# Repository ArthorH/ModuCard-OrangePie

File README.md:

# ModuCard System Orange PI 5 pro adapter

## Project Status: **Ongoing**  
### REV C
**Design** ⏳ — **Fabrication** ⏳ — **Assembly** ⏳ — **Bringup** ⏳ — **Testing** ⏳
### REV B
**Design** ✅ — **Fabrication** ✅ — **Assembly** ✅ — **Bringup** ✅ — **Testing** ⛔ 
Failed: https://github.com/ArthorH/ModuCard-OrangePie/issues/6
### REV A
**Design** ✅ — **Fabrication** ✅ — **Assembly** ✅ — **Bringup** ✅ — **Testing done** ✅ 
## Key technologies:
&nbsp;&nbsp;&nbsp;&nbsp; &nbsp;&nbsp;&nbsp;&nbsp; &nbsp;&nbsp;&nbsp;&nbsp;
# Features

- 5V 8A psu for Orange PI
- Embedded USB audo interface
- Embedded USB CAN adapter
- External Fan controller
- UART debug interface
  
# Block Diagram
&nbsp;&nbsp;&nbsp;&nbsp;

# Manufactured board

# Moducard OrangePie in Zwentendorf Austria!

### Check out other projects

Orange Pie ->  https://github.com/ArthorH/ModuCard-OrangePie

ModuCard Base module -> https://github.com/ArthorH/ModuCard-base-module

ModuCard Backplane -> https://github.com/ArthorH/ModuCard-backplane

# Author
Artem Horiunov
# License 
To be added

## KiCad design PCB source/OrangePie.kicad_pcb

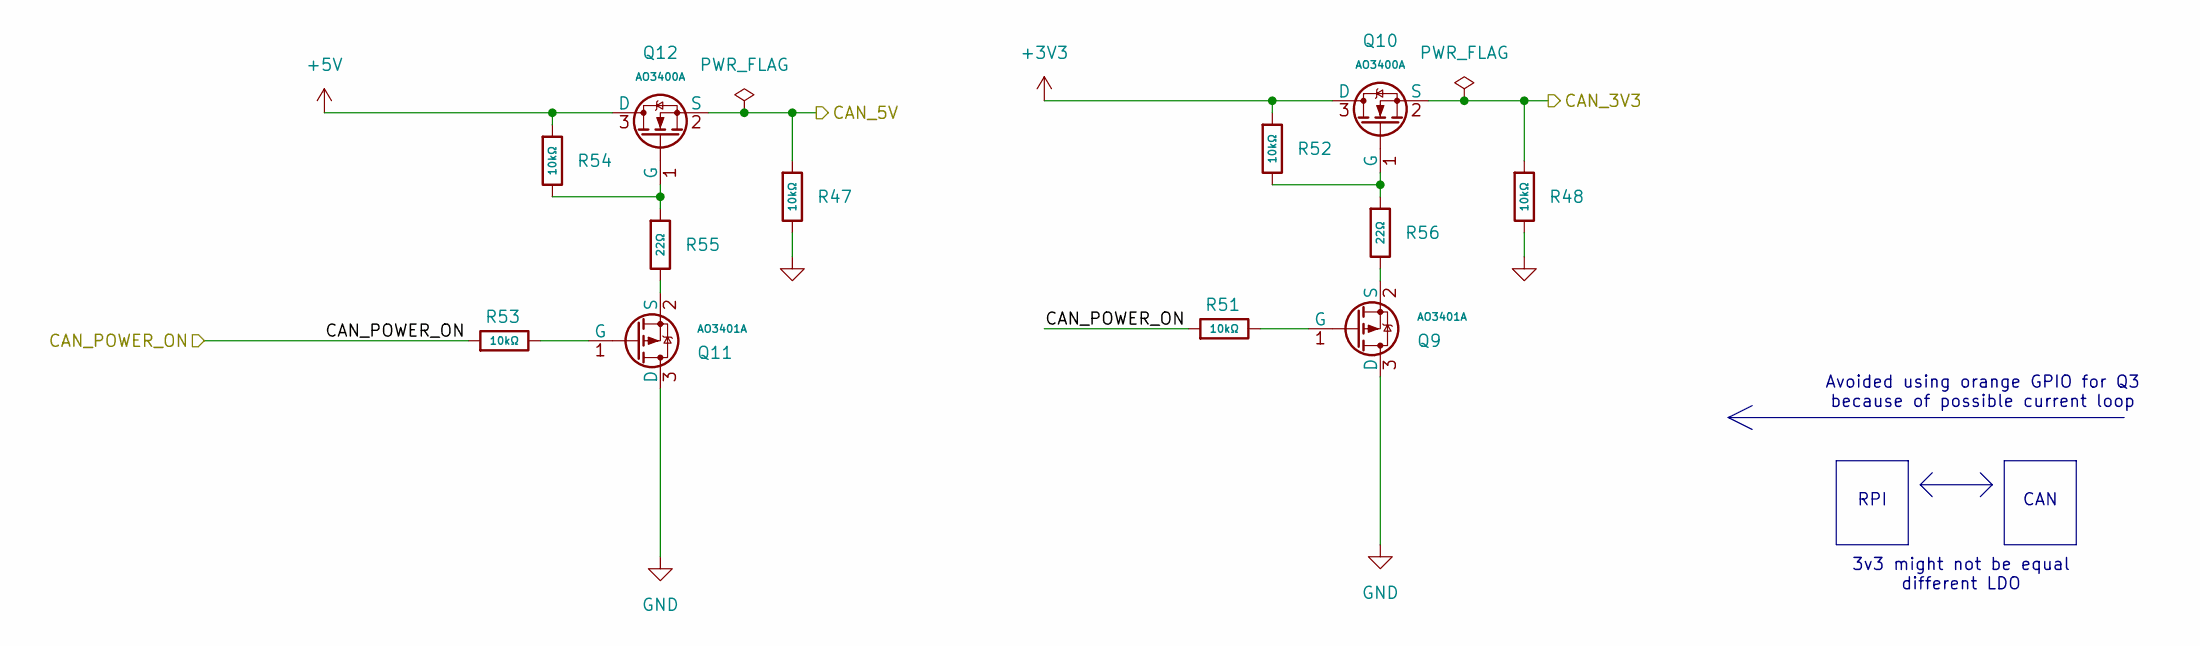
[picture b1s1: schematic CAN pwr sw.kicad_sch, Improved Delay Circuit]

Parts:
Q9, Q11: AO3401A; Q_SOT-23; Part AO3401A; LCSC C15127
Q10, Q12: AO3400A; Q_SOT-23; Part AO3400A; LCSC C20917
R47, R48, R51, R52, R53, R54: 10kΩ; R_0402; Overload Voltage (Max) 50V; Tolerance ±1%; Part 0402WGF1002TCE; LCSC C25744
R55, R56: 22Ω; R_0402; Overload Voltage (Max) 50V; Tolerance ±1%; Part 0402WGF220JTCE; LCSC C25092

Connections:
+3V3: Q10.3 (D), R52.1; also elsewhere on the board
+5V: Q12.3 (D), R54.1; also elsewhere on the board
/CAN pwr sw/CAN_3V3: Q10.2 (S), R48.1; also elsewhere on the board
/CAN pwr sw/CAN_5V: Q12.2 (S), R47.1; also elsewhere on the board
/CAN pwr sw/CAN_POWER_ON: R51.1, R53.1; also elsewhere on the board
GND: Q9.3 (D), Q11.3 (D), R47.2, R48.2; also elsewhere on the board
unnamed: Q9.1 (G), R51.2
unnamed: Q9.2 (S), R56.2
unnamed: Q10.1 (G), R52.2, R56.1
unnamed: Q11.1 (G), R53.2
unnamed: Q11.2 (S), R55.2
unnamed: Q12.1 (G), R54.2, R55.1

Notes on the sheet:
Avoided using orange GPIO for Q3 because of possible current loop
CAN
RPI
3v3 might not be equal different LDO

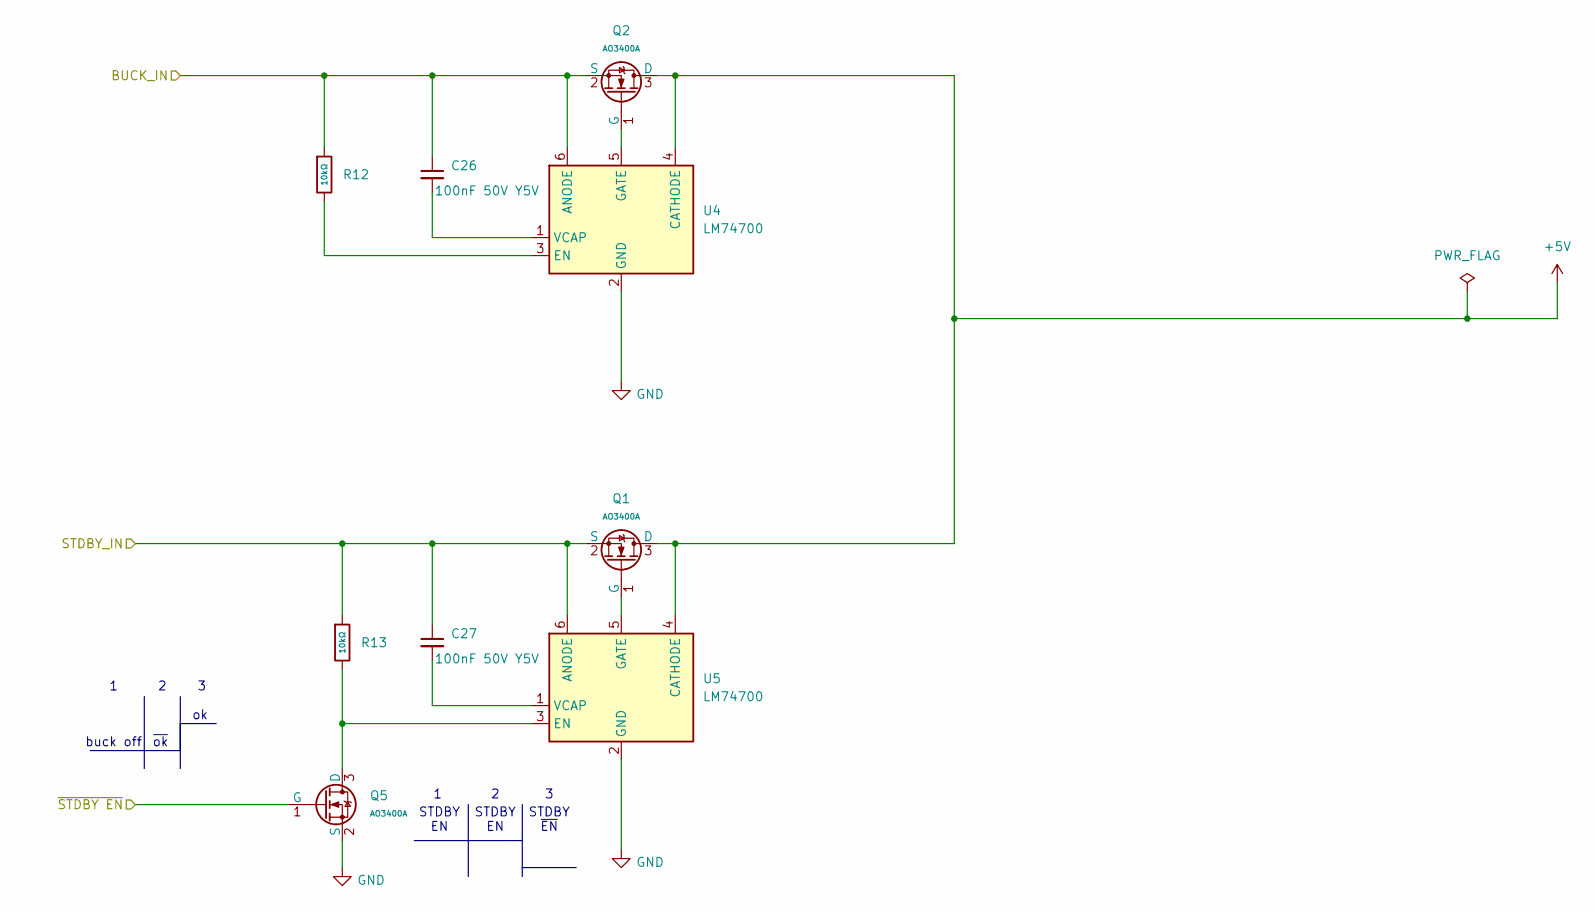
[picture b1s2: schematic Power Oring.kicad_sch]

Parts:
C26, C27: 100nF 50V Y5V; C_0402_1005Metric
Q1, Q2, Q5: AO3400A; Q_SOT-23; Part AO3400A; LCSC C20917
R12, R13: 10kΩ; R_0402; Overload Voltage (Max) 50V; Tolerance ±1%; Part 0402WGF1002TCE; LCSC C25744
U4, U5: LM74700; SOT-23-6

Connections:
+5V: Q1.3 (D), Q2.3 (D), U4.4 (CATHODE), U5.4 (CATHODE); also elsewhere on the board
/5v buck/BUCK_OUT: C26.1, Q2.2 (S), R12.1, U4.6 (ANODE); also elsewhere on the board
/5v buck/Pgood: Q5.1 (G); also elsewhere on the board
/DIN41612 connector/5v_STDBY: C27.1, Q1.2 (S), R13.1, U5.6 (ANODE); also elsewhere on the board
GND: Q5.2 (S), U4.2 (GND), U5.2 (GND); also elsewhere on the board
unnamed: Q1.1 (G), U5.5 (GATE)
unnamed: Q2.1 (G), U4.5 (GATE)
unnamed: Q5.3 (D), R13.2, U5.3 (EN)
unnamed: R12.2, U4.3 (EN)
unnamed: C26.2, U4.1 (VCAP)
unnamed: C27.2, U5.1 (VCAP)

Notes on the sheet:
buck off
~{ok}
STDBY EN
STDBY ~{EN}

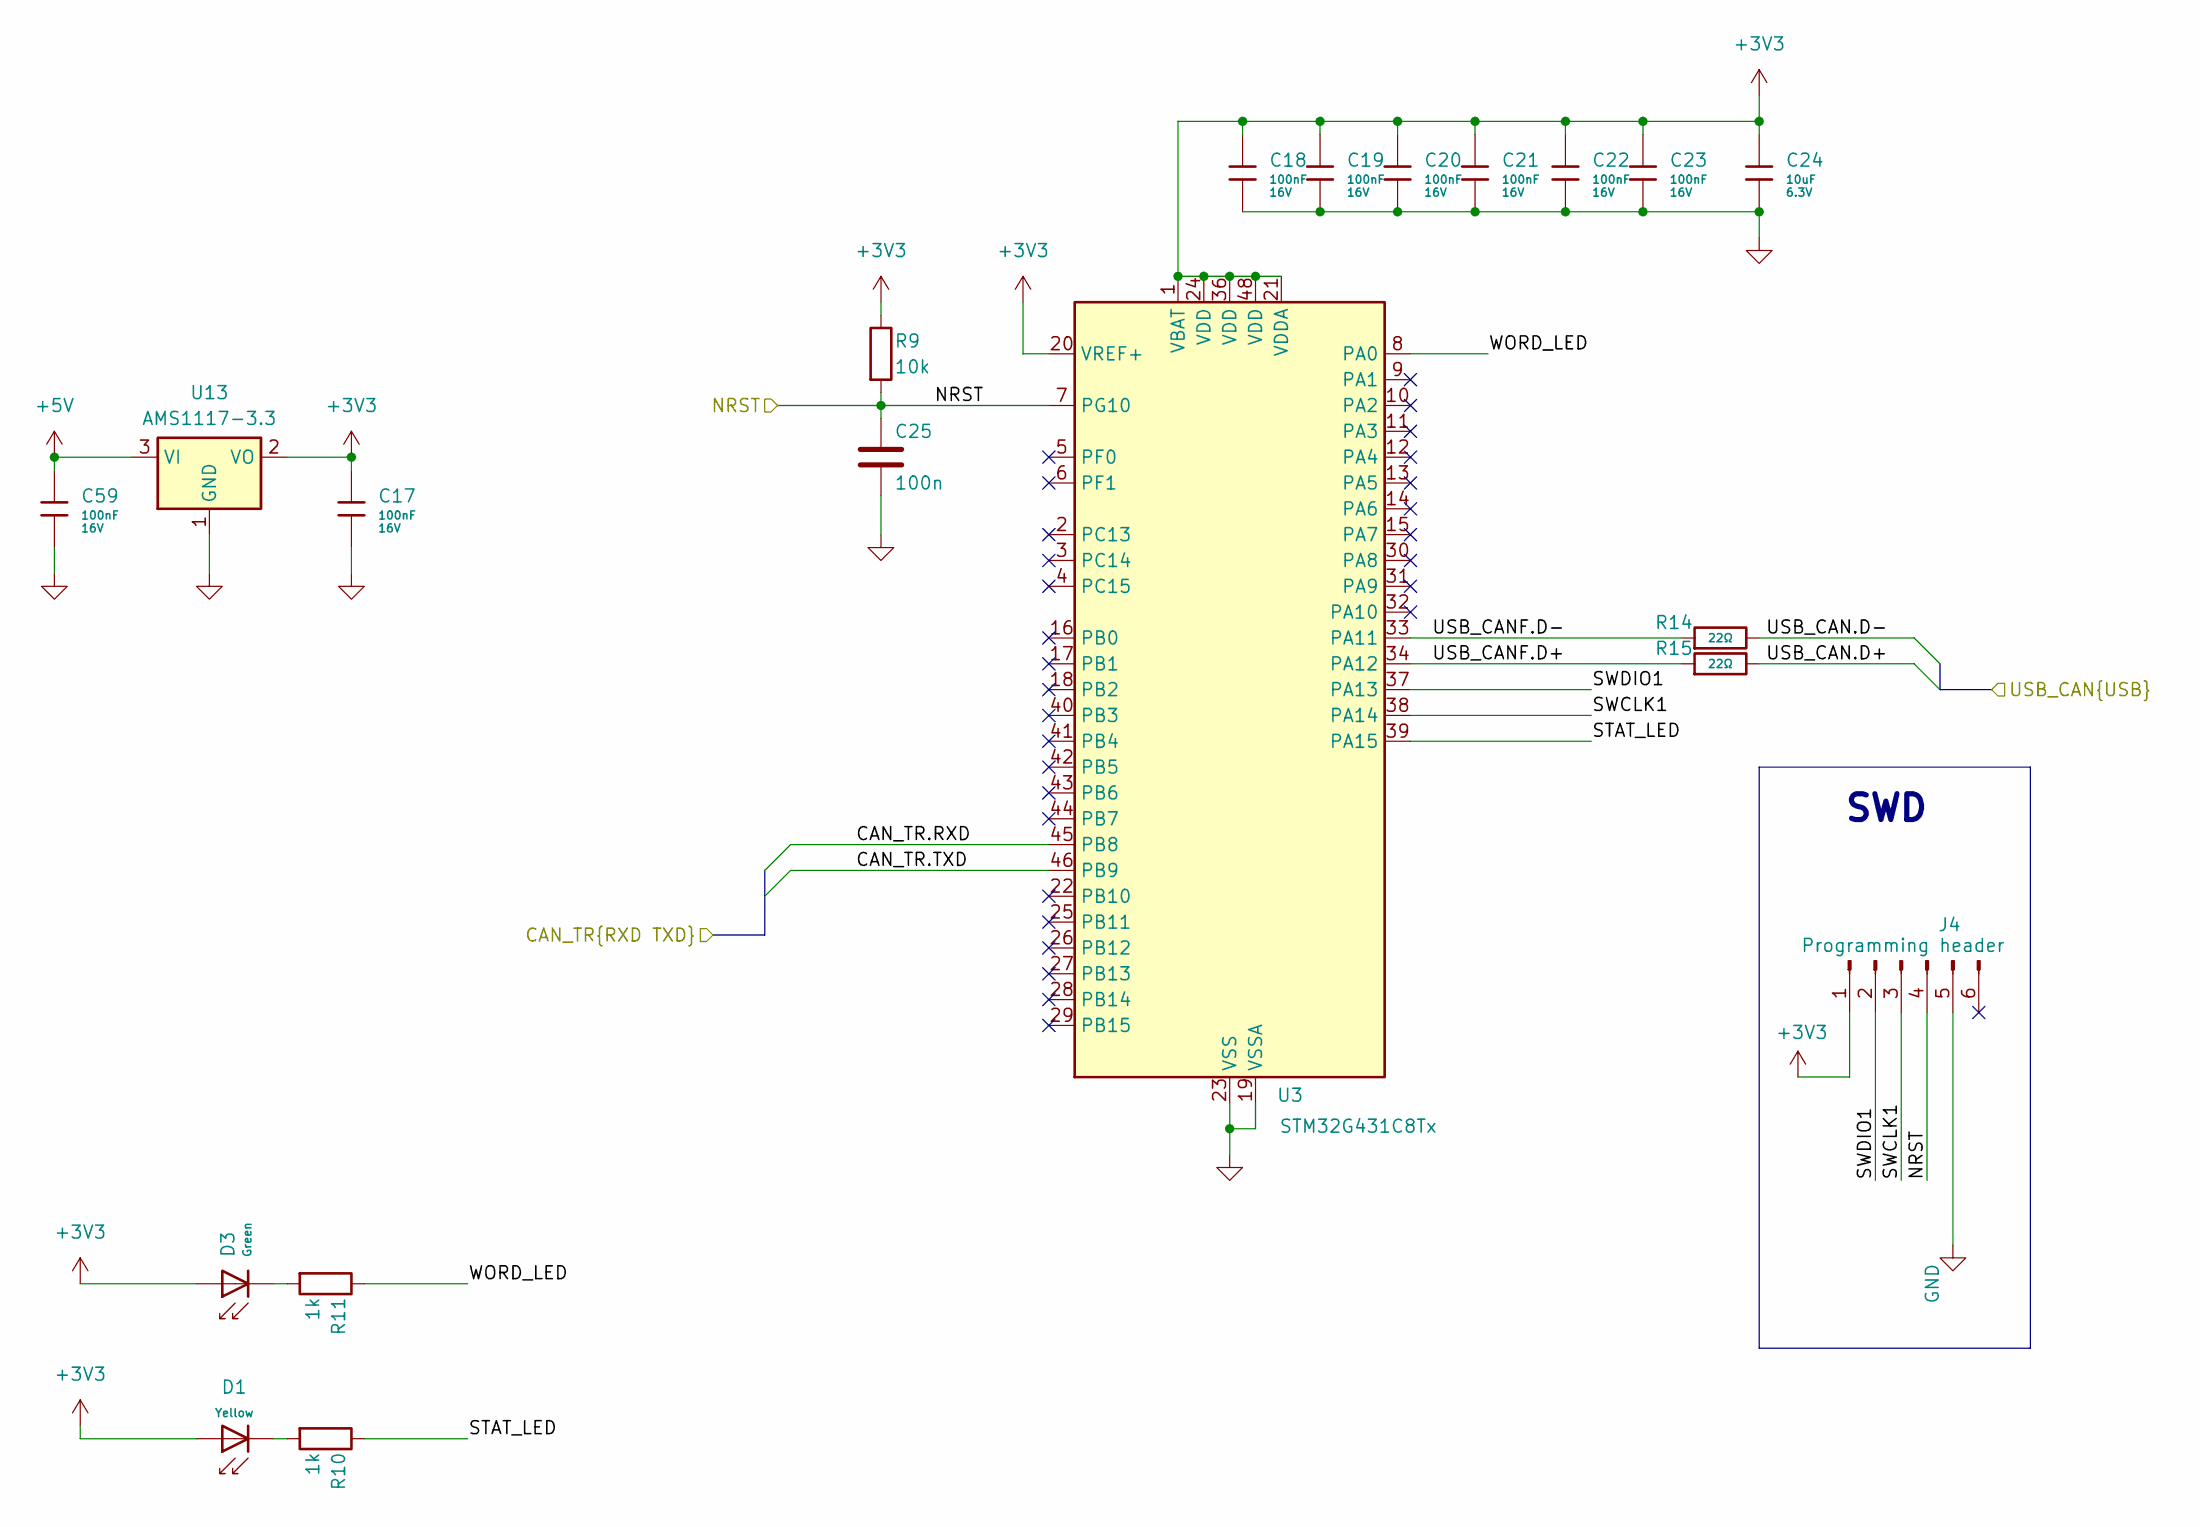
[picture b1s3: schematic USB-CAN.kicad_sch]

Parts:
C17, C18, C19, C20, C21, C22, C23, C59: 100nF; C_0402; Voltage Rated 16V; Tolerance ±10%; Part CL05B104KO5NNNC; LCSC C1525
C24: 10uF; C_0402; Voltage Rated 6.3V; Tolerance ±20%; Part CL05A106MQ5NUNC; LCSC C15525
C25: 100n; C_0402_1005Metric
D1: Yellow; D_0603; Part 19-213/Y2C-CQ2R2L/3T(CY); LCSC C72038
D3: Green; D_0603; Part 19-217/GHC-YR1S2/6T; LCSC C2986059
J4: Programming header; PinHeader_1x06_P1.27mm_Vertical
R9: 10k; R_0402_1005Metric
R10, R11: 1k; R_0402_1005Metric
R14, R15: 22Ω; R_0402; Overload Voltage (Max) 50V; Tolerance ±1%; Part 0402WGF220JTCE; LCSC C25092
U3: STM32G431C8Tx; LQFP-48_7x7mm_P0.5mm
U13: AMS1117-3.3; SOT-223-3_TabPin2

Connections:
+3V3: C17.1, C18.1, C19.1, C20.1, C21.1, C22.1, C23.1, C24.1, D1.2, D3.2, J4.1, R9.1, U3.1 (VBAT), U3.20 (VREF+), U3.21 (VDDA), U3.24 (VDD), U3.36 (VDD), U3.48 (VDD), U13.2 (VO); also elsewhere on the board
+5V: C59.1, U13.3 (VI); also elsewhere on the board
/Can Transiver1/CAN_TR.RXD: U3.45 (PB8); also elsewhere on the board
/Can Transiver1/CAN_TR.TXD: U3.46 (PB9); also elsewhere on the board
/USB HUB/USB_CAN.D+: R15.2; also elsewhere on the board
/USB HUB/USB_CAN.D-: R14.2; also elsewhere on the board
/USB-CAN/NRST: C25.1, J4.4, R9.2, U3.7 (PG10); also elsewhere on the board
/USB-CAN/STAT_LED: R10.1, U3.39 (PA15)
/USB-CAN/SWCLK1: J4.3, U3.38 (PA14)
/USB-CAN/SWDIO1: J4.2, U3.37 (PA13)
/USB-CAN/USB_CANF.D+: R15.1, U3.34 (PA12)
/USB-CAN/USB_CANF.D-: R14.1, U3.33 (PA11)
/USB-CAN/WORD_LED: R11.1, U3.8 (PA0)
GND: C17.2, C18.2, C19.2, C20.2, C21.2, C22.2, C23.2, C24.2, C25.2, C59.2, J4.5, U3.19 (VSSA), U3.23 (VSS), U3.35 (VSS), U3.47 (VSS), U13.1 (GND); also elsewhere on the board
unnamed: D1.1, R10.2
unnamed: D3.1, R11.2

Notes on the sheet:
SWD

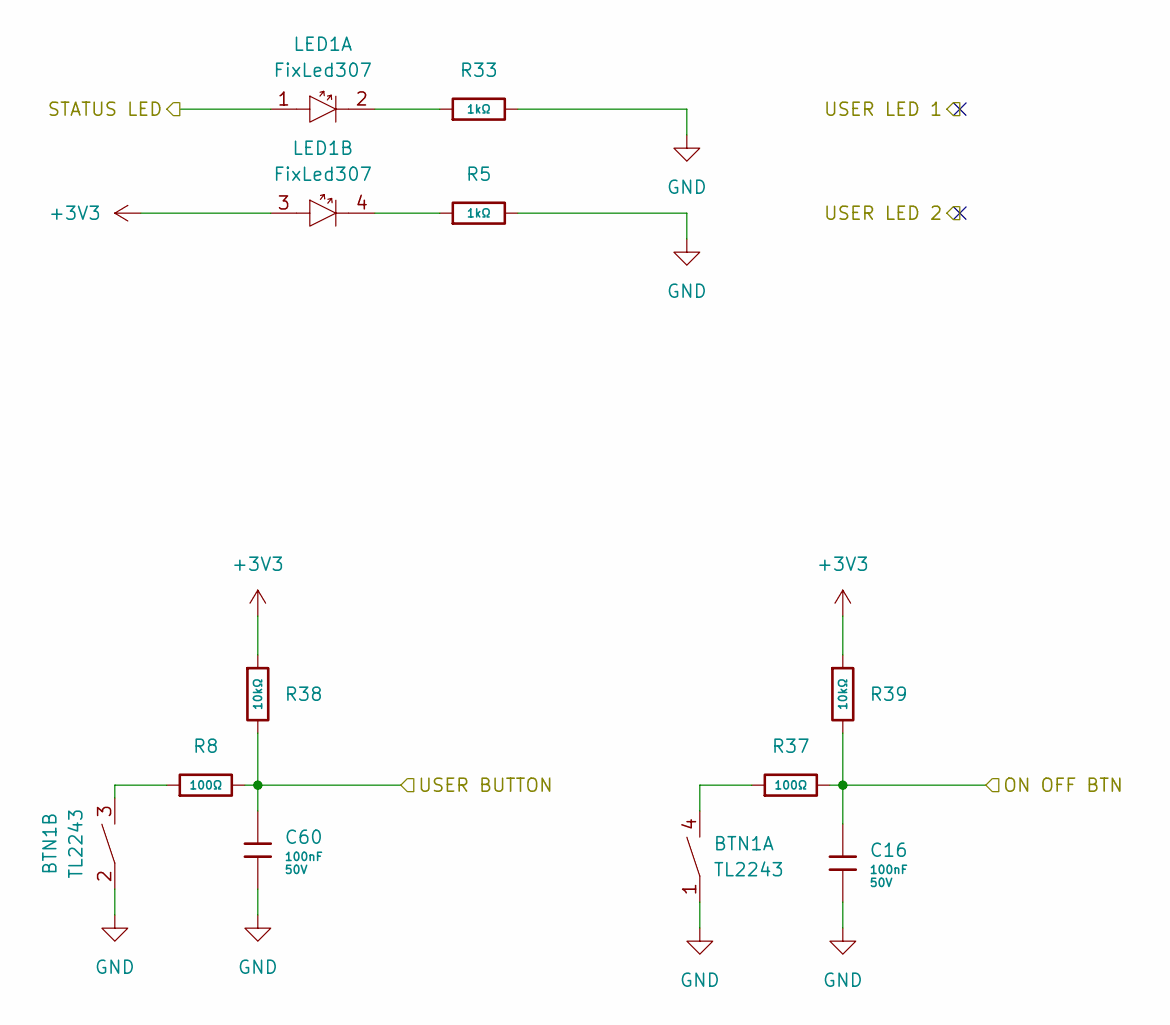
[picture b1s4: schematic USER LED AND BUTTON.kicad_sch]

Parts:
BTN1: TL2243
C16, C60: 100nF; C_0402; Voltage Rated 50V; Tolerance ±10%; Part CL05B104KB54PNC; LCSC C307331
LED1: FixLed307
R5, R33: 1kΩ; R_0402; Overload Voltage (Max) 50V; Tolerance ±1%; Part 0402WGF1001TCE; LCSC C11702
R8, R37: 100Ω; R_0402; Overload Voltage (Max) 50V; Tolerance ±1%; Part 0402WGF1000TCE; LCSC C25076
R38, R39: 10kΩ; R_0402; Overload Voltage (Max) 50V; Tolerance ±1%; Part 0402WGF1002TCE; LCSC C25744

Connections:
+3V3: LED1.3, R38.1, R39.1; also elsewhere on the board
/OrangePi 5 pro Header/ON OFF BTN: C16.1, R37.2, R39.2; also elsewhere on the board
/OrangePi 5 pro Header/STATUS LED: LED1.1; also elsewhere on the board
/OrangePi 5 pro Header/USER BUTTON: C60.1, R8.2, R38.2; also elsewhere on the board
GND: BTN1.1, BTN1.2, C16.2, C60.2, R5.2, R33.2; also elsewhere on the board
unnamed: BTN1.3, R8.1
unnamed: BTN1.4, R37.1
unnamed: LED1.2, R33.1
unnamed: LED1.4, R5.1

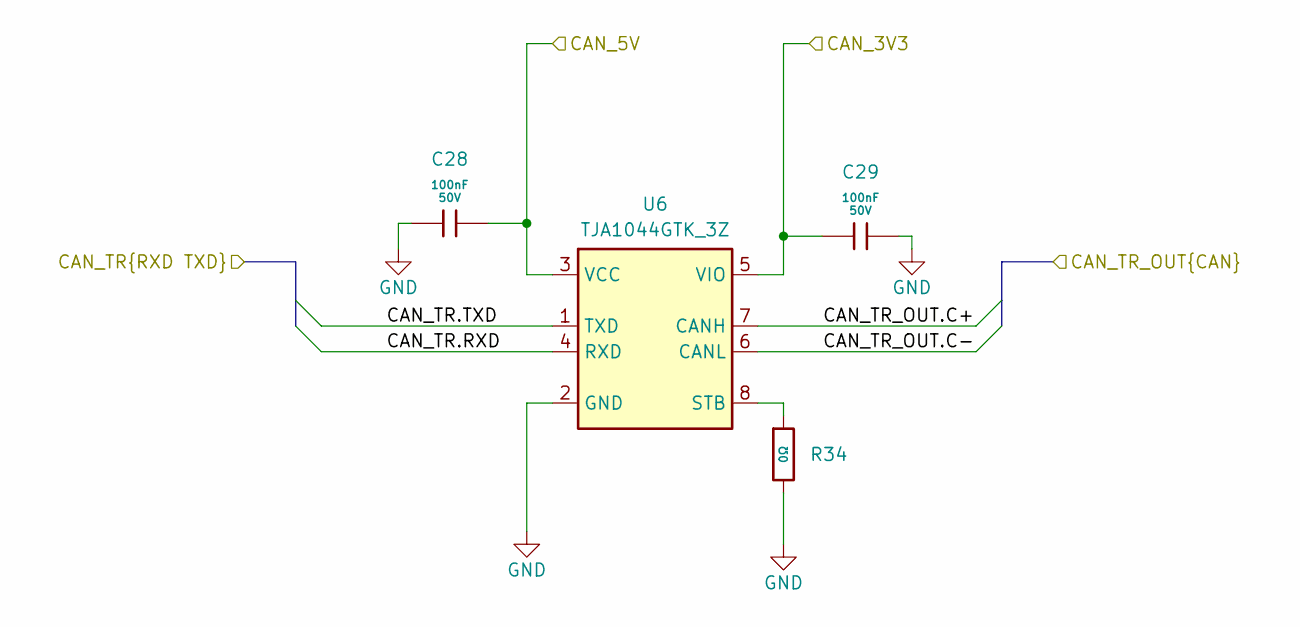
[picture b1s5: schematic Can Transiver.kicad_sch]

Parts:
C28, C29: 100nF; C_0402; Voltage Rated 50V; Tolerance ±10%; Part CL05B104KB54PNC; LCSC C307331
R34: 0Ω; R_0402; Overload Voltage (Max) 50V; Tolerance ±1%; Part 0402WGF0000TCE; LCSC C17168
U6: TJA1044GTK_3Z; HVSON-8-1EP_3x3mm_P0.65mm_EP1.6x2.4mm; Manufacturer_Part_Number TJA1044GTK/3Z

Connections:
/CAN pwr sw/CAN_3V3: C29.1, U6.5 (VIO); also elsewhere on the board
/CAN pwr sw/CAN_5V: C28.2, U6.3 (VCC); also elsewhere on the board
/Can Transiver/CAN_TR.RXD: U6.4 (RXD); also elsewhere on the board
/Can Transiver/CAN_TR.TXD: U6.1 (TXD); also elsewhere on the board
/Can Transiver/CAN_TR_OUT.C+: U6.7 (CANH); also elsewhere on the board
/Can Transiver/CAN_TR_OUT.C-: U6.6 (CANL); also elsewhere on the board
GND: C28.1, C29.2, R34.2, U6.2 (GND), U6.9 (EP); also elsewhere on the board
unnamed: R34.1, U6.8 (STB)

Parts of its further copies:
C30, C31: 100nF; C_0402; Voltage Rated 50V; Tolerance ±10%; Part CL05B104KB54PNC; LCSC C307331
R35: 0Ω; R_0402; Overload Voltage (Max) 50V; Tolerance ±1%; Part 0402WGF0000TCE; LCSC C17168
U7: TJA1044GTK_3Z; HVSON-8-1EP_3x3mm_P0.65mm_EP1.6x2.4mm; Manufacturer_Part_Number TJA1044GTK/3Z

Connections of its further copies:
/CAN pwr sw/CAN_3V3: C31.1, U7.5 (VIO); also elsewhere on the board
/CAN pwr sw/CAN_5V: C30.2, U7.3 (VCC); also elsewhere on the board
/Can Transiver1/CAN_TR.RXD: U7.4 (RXD); also elsewhere on the board
/Can Transiver1/CAN_TR.TXD: U7.1 (TXD); also elsewhere on the board
/Can Transiver1/CAN_TR_OUT.C+: U7.7 (CANH); also elsewhere on the board
/Can Transiver1/CAN_TR_OUT.C-: U7.6 (CANL); also elsewhere on the board
GND: C30.1, C31.2, R35.2, U7.2 (GND), U7.9 (EP); also elsewhere on the board
unnamed: R35.1, U7.8 (STB)

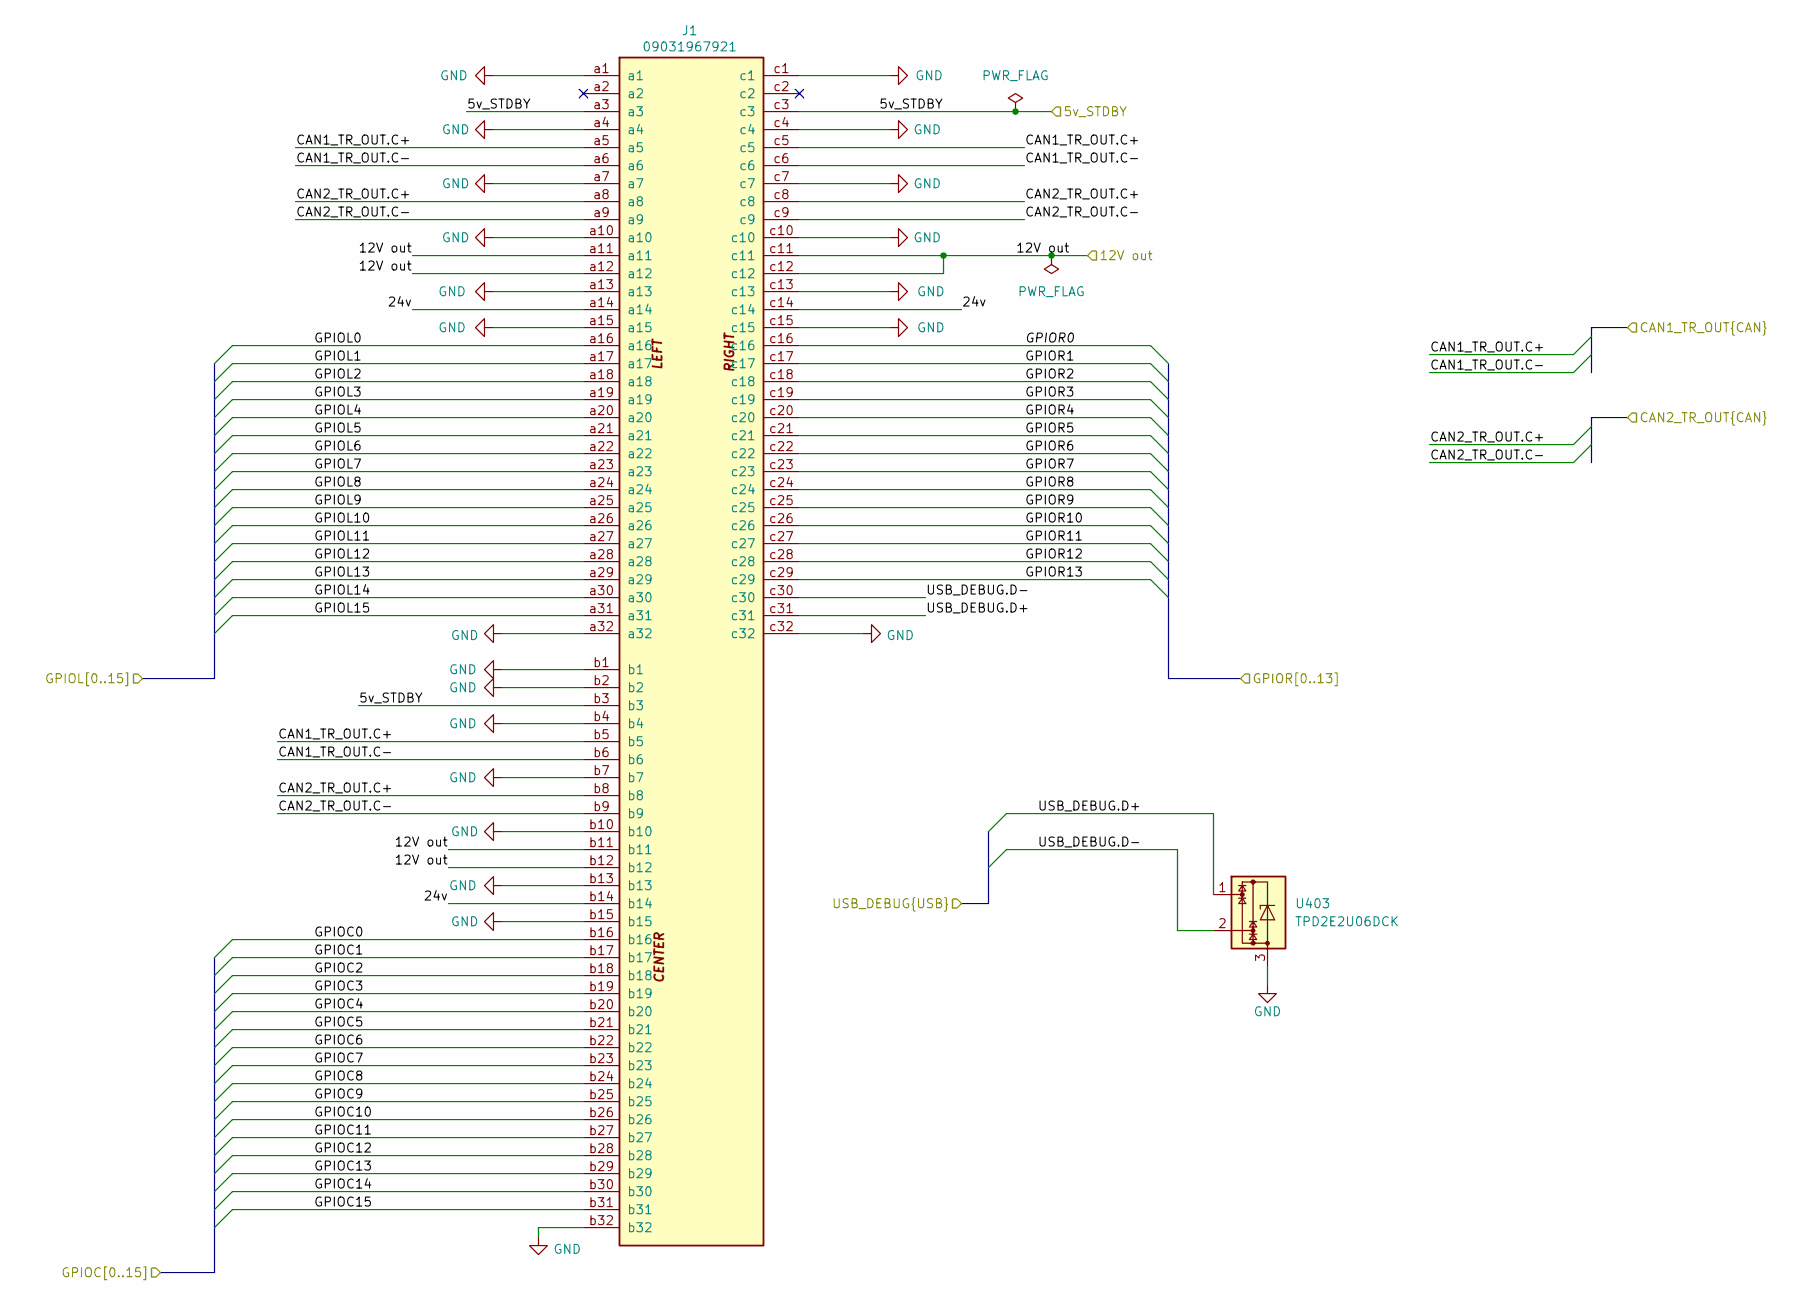
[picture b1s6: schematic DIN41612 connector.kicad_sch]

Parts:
J1: 09031967921; DIN41612_R_3x32_Female_Horizontal_THT; PARTREV D
U403: TPD2E2U06DCK; SOT-323_SC-70

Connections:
/5v buck/V_{IN}: J1.a11, J1.a12, J1.b11, J1.b12, J1.c11, J1.c12; also elsewhere on the board
/Can Transiver1/CAN_TR_OUT.C+: J1.a8, J1.b8, J1.c8; also elsewhere on the board
/Can Transiver1/CAN_TR_OUT.C-: J1.a9, J1.b9, J1.c9; also elsewhere on the board
/Can Transiver/CAN_TR_OUT.C+: J1.a5, J1.b5, J1.c5; also elsewhere on the board
/Can Transiver/CAN_TR_OUT.C-: J1.a6, J1.b6, J1.c6; also elsewhere on the board
/DIN41612 connector/5v_STDBY: J1.a3, J1.b3, J1.c3; also elsewhere on the board
/DIN41612 connector/24v: J1.a14, J1.b14, J1.c14
/DIN41612 connector/GPIOC0: J1.b16
/DIN41612 connector/GPIOC1: J1.b17
/DIN41612 connector/GPIOC2: J1.b18
/DIN41612 connector/GPIOC3: J1.b19
/DIN41612 connector/GPIOC4: J1.b20
/DIN41612 connector/GPIOC5: J1.b21
/DIN41612 connector/GPIOC6: J1.b22
/DIN41612 connector/GPIOC7: J1.b23
/DIN41612 connector/GPIOC8: J1.b24
/DIN41612 connector/GPIOC9: J1.b25
/DIN41612 connector/GPIOC10: J1.b26
/DIN41612 connector/GPIOC11: J1.b27
/DIN41612 connector/GPIOC12: J1.b28
/DIN41612 connector/GPIOC13: J1.b29
/DIN41612 connector/GPIOC14: J1.b30
/DIN41612 connector/GPIOC15: J1.b31
/DIN41612 connector/GPIOL0: J1.a16
/DIN41612 connector/GPIOL1: J1.a17
/DIN41612 connector/GPIOL2: J1.a18
/DIN41612 connector/GPIOL3: J1.a19
/DIN41612 connector/GPIOL4: J1.a20
/DIN41612 connector/GPIOL5: J1.a21
/DIN41612 connector/GPIOL6: J1.a22
/DIN41612 connector/GPIOL7: J1.a23
/DIN41612 connector/GPIOL8: J1.a24
/DIN41612 connector/GPIOL9: J1.a25
/DIN41612 connector/GPIOL10: J1.a26
/DIN41612 connector/GPIOL11: J1.a27
/DIN41612 connector/GPIOL12: J1.a28
/DIN41612 connector/GPIOL13: J1.a29
/DIN41612 connector/GPIOL14: J1.a30
/DIN41612 connector/GPIOL15: J1.a31
/DIN41612 connector/GPIOR0: J1.c16
/DIN41612 connector/GPIOR1: J1.c17
/DIN41612 connector/GPIOR2: J1.c18
/DIN41612 connector/GPIOR3: J1.c19
/DIN41612 connector/GPIOR4: J1.c20
/DIN41612 connector/GPIOR5: J1.c21
/DIN41612 connector/GPIOR6: J1.c22
/DIN41612 connector/GPIOR7: J1.c23
/DIN41612 connector/GPIOR8: J1.c24
/DIN41612 connector/GPIOR9: J1.c25
/DIN41612 connector/GPIOR10: J1.c26
/DIN41612 connector/GPIOR11: J1.c27
/DIN41612 connector/GPIOR12: J1.c28
/DIN41612 connector/GPIOR13: J1.c29
/DIN41612 connector/USB_DEBUG.D+: J1.c31, U403.1; also elsewhere on the board
/DIN41612 connector/USB_DEBUG.D-: J1.c30, U403.2; also elsewhere on the board
GND: J1.a1, J1.a4, J1.a7, J1.a10, J1.a13, J1.a15, J1.a32, J1.b1, J1.b2, J1.b4, J1.b7, J1.b10, J1.b13, J1.b15, J1.b32, J1.c1, J1.c4, J1.c7, J1.c10, J1.c13, J1.c15, J1.c32, U403.3; also elsewhere on the board

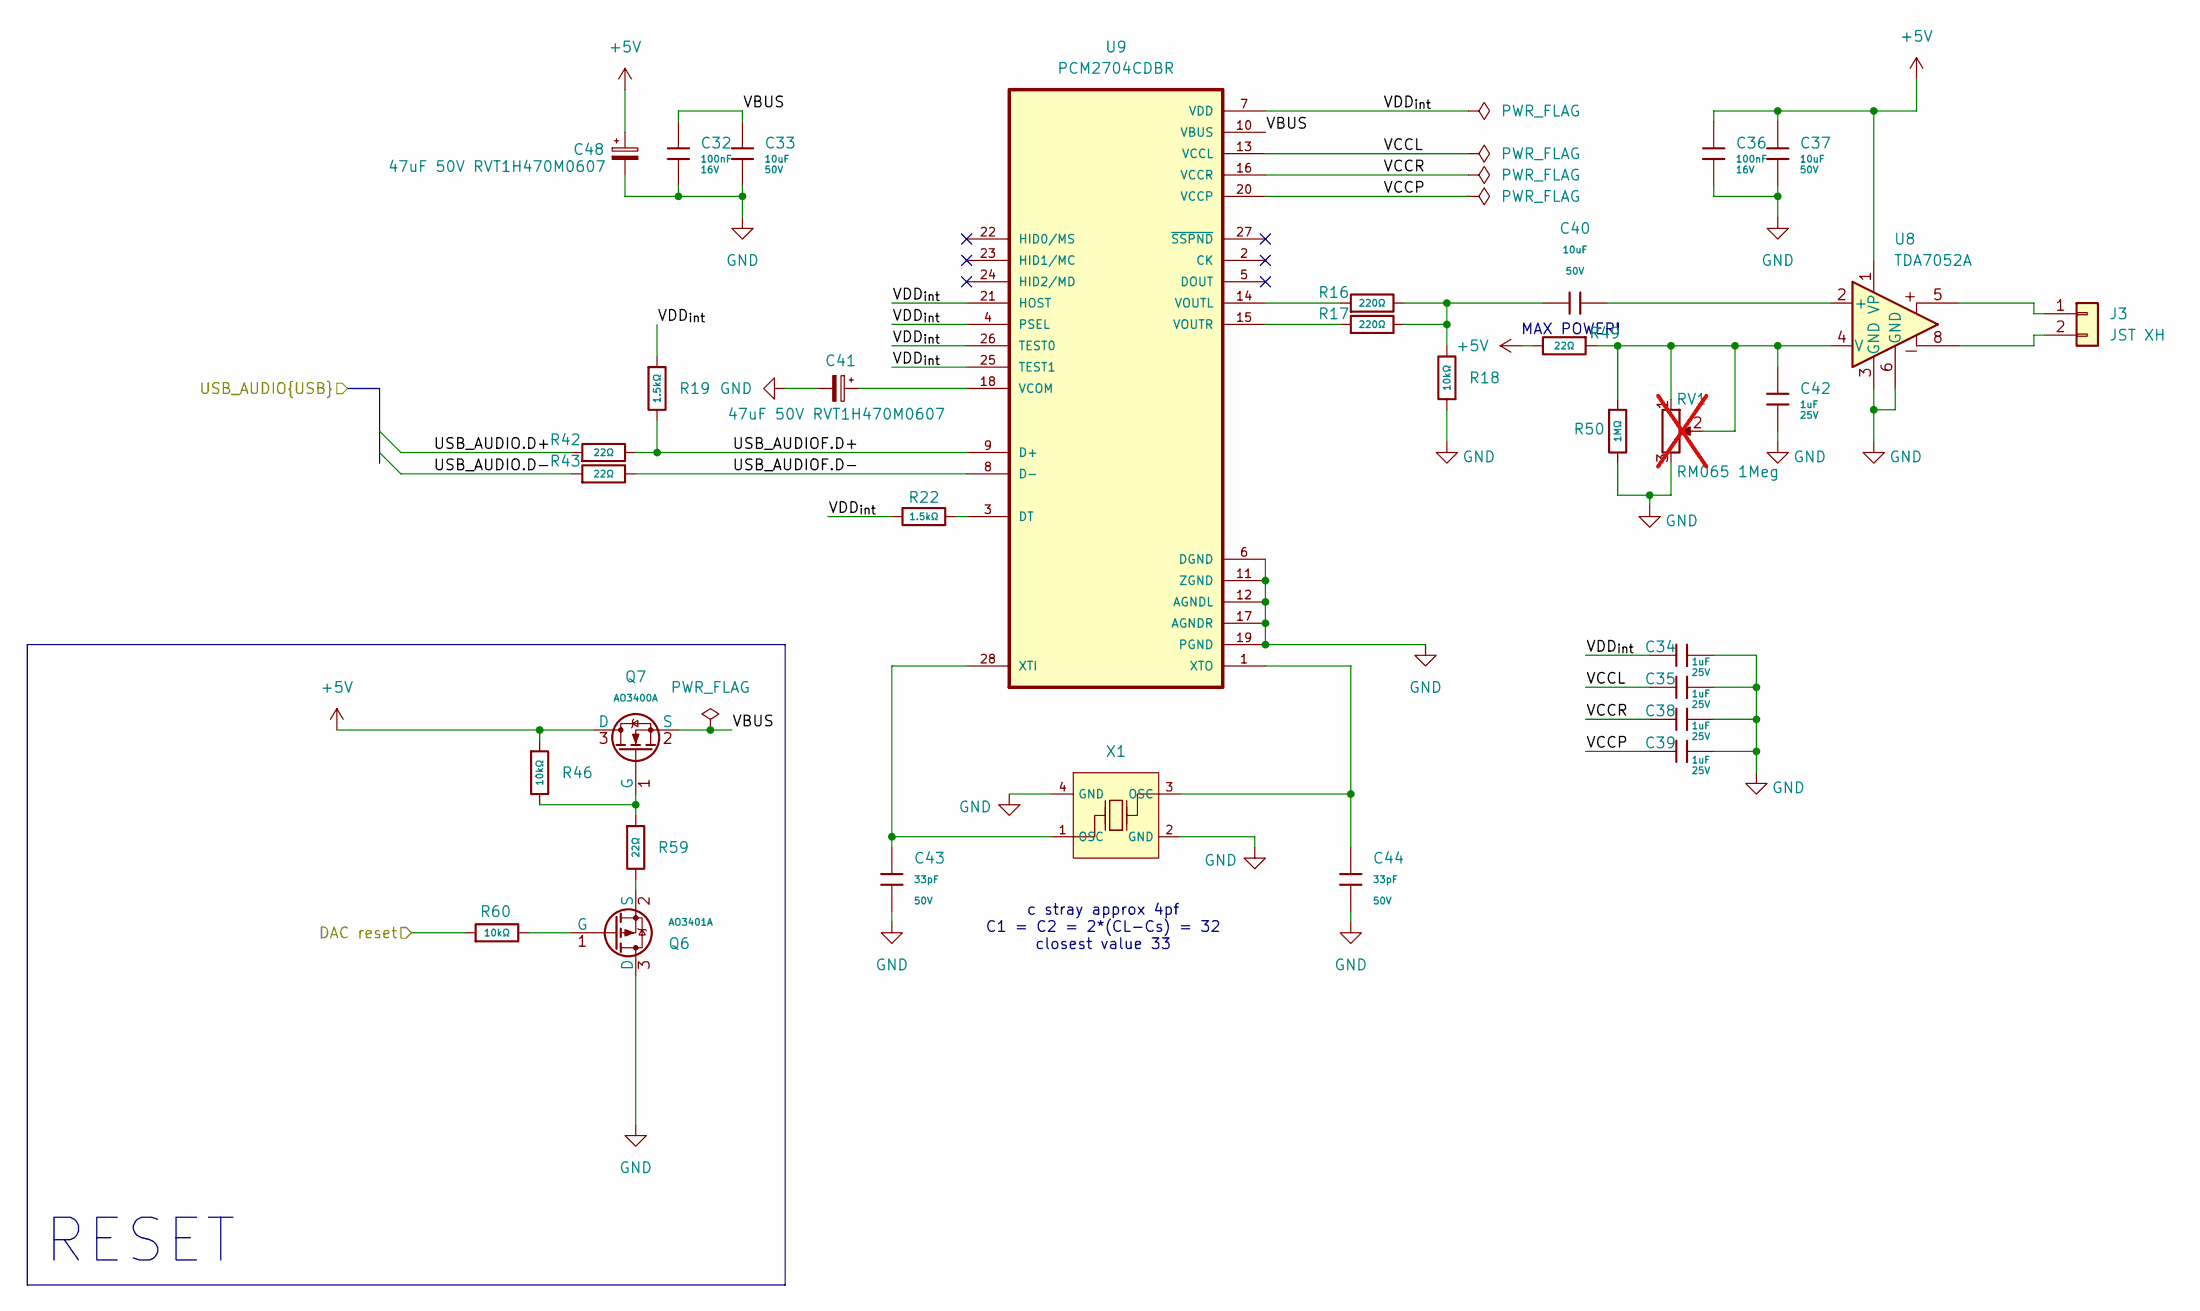
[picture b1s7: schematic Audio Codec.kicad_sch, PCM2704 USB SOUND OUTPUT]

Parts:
C32, C36: 100nF; C_0402; Voltage Rated 16V; Tolerance ±10%; Part CL05B104KO5NNNC; LCSC C1525
C33, C37, C40: 10uF; C_0805; Voltage Rated 50V; Tolerance ±10%; Part GRM21BR61H106KE43L; LCSC C440198
C34, C35, C38, C39, C42: 1uF; C_0402; Voltage Rated 25V; Tolerance ±10%; Part CL05A105KA5NQNC; LCSC C52923
C41, C48: 47uF 50V RVT1H470M0607; CP_Elec_6.3x7.7
C43, C44: 33pF; C_0402; Voltage Rated 50V; Tolerance ±5%; Part 0402CG330J500NT; LCSC C1562
J3: JST XH; JST_XH_B2B-XH-AM_1x02_P2.50mm_Vertical
Q6: AO3401A; Q_SOT-23; Part AO3401A; LCSC C15127
Q7: AO3400A; Q_SOT-23; Part AO3400A; LCSC C20917
R16, R17: 220Ω; R_0402; Overload Voltage (Max) 50V; Tolerance ±1%; Part 0402WGF2200TCE; LCSC C25091
R18, R46, R60: 10kΩ; R_0402; Overload Voltage (Max) 50V; Tolerance ±1%; Part 0402WGF1002TCE; LCSC C25744
R19, R22: 1.5kΩ; R_0402; Overload Voltage (Max) 50V; Tolerance ±1%; Part 0402WGF1501TCE; LCSC C25867
R42, R43, R49, R59: 22Ω; R_0402; Overload Voltage (Max) 50V; Tolerance ±1%; Part 0402WGF220JTCE; LCSC C25092
R50: 1MΩ; R_0402; Overload Voltage (Max) 50V; Tolerance ±1%; Part 0402WGF1004TCE; LCSC C26083
RV1: RM065 1Meg; Potentiometer_Runtron_RM-065_Vertical; not fitted
U8: TDA7052A; SO-8_3.9x4.9mm_P1.27mm
U9: PCM2704CDBR; SSOP-28_5.3x10.2mm_P0.65mm
X1: X322512MSB4SI; CRYSTAL-SMD_4P-L3.2-W2.5-BL; Frequency Tolerance ±10ppm; Part X322512MSB4SI; LCSC C9002

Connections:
+5V: C36.1, C37.2, C48.1, Q7.3 (D), R46.1, R49.2, U8.1 (VP); also elsewhere on the board
/Audio Codec/DAC reset: R60.1; also elsewhere on the board
/Audio Codec/USB_AUDIO.D+: R42.1; also elsewhere on the board
/Audio Codec/USB_AUDIO.D-: R43.1; also elsewhere on the board
/Audio Codec/USB_AUDIOF.D+: R19.2, R42.2, U9.9 (D+)
/Audio Codec/USB_AUDIOF.D-: R43.2, U9.8 (D-)
/Audio Codec/VBUS: C32.1, C33.2, Q7.2 (S), U9.10 (VBUS)
/Audio Codec/VCCL: C35.1, U9.13 (VCCL)
/Audio Codec/VCCP: C39.1, U9.20 (VCCP)
/Audio Codec/VCCR: C38.1, U9.16 (VCCR)
/Audio Codec/VDD_{int}: C34.1, R19.1, R22.2, U9.4 (PSEL), U9.7 (VDD), U9.21 (HOST), U9.25 (TEST1), U9.26 (TEST0)
GND: C32.2, C33.1, C34.2, C35.2, C36.2, C37.1, C38.2, C39.2, C41.2, C42.2, C43.2, C44.2, C48.2, Q6.3 (D), R18.1, R50.2, RV1.3, U8.3 (GND), U8.6 (GND), U9.6 (DGND), U9.11 (ZGND), U9.12 (AGNDL), U9.17 (AGNDR), U9.19 (PGND), X1.2 (GND), X1.4 (GND); also elsewhere on the board
unnamed: C40.2, R16.2, R17.2, R18.2
unnamed: J3.1, U8.5
unnamed: J3.2, U8.8
unnamed: Q6.1 (G), R60.2
unnamed: Q6.2 (S), R59.2
unnamed: Q7.1 (G), R46.2, R59.1
unnamed: C40.1, U8.2 (+)
unnamed: C42.1, R49.1, R50.1, RV1.1, RV1.2, U8.4 (V)
unnamed: R22.1, U9.3 (DT)
unnamed: C41.1, U9.18 (VCOM)
unnamed: R16.1, U9.14 (VOUTL)
unnamed: R17.1, U9.15 (VOUTR)
unnamed: C43.1, U9.28 (XTI), X1.1 (OSC)
unnamed: C44.1, U9.1 (XTO), X1.3 (OSC)

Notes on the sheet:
RESET
MAX POWER!
c stray approx 4pf C1 = C2 = 2*(CL-Cs) = 32 closest value 33

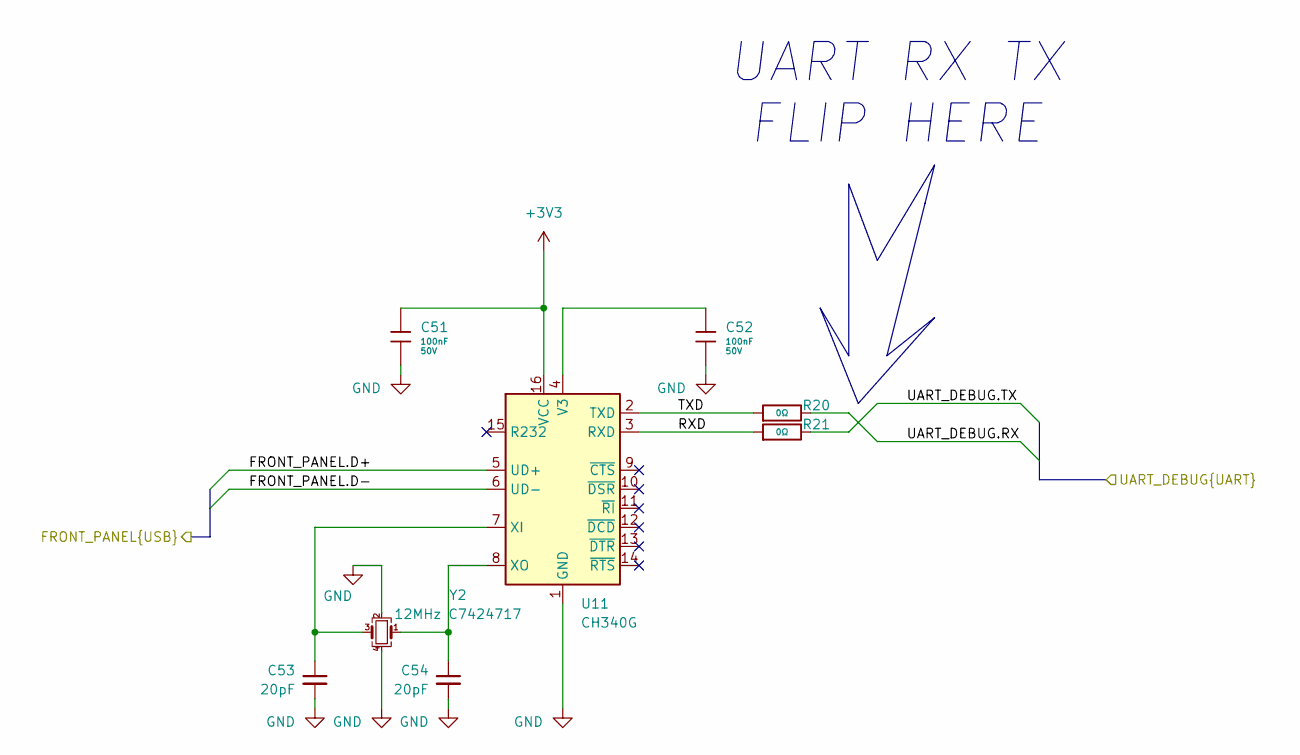
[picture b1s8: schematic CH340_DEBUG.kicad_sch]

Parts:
C51, C52: 100nF; C_0402; Voltage Rated 50V; Tolerance ±10%; Part CL05B104KB54PNC; LCSC C307331
C53, C54: 20pF; C_0402_1005Metric
R20, R21: 0Ω; R_0402; Overload Voltage (Max) 50V; Tolerance ±1%; Part 0402WGF0000TCE; LCSC C17168
U11: CH340G; SOIC-16_3.9x9.9mm_P1.27mm
Y2: 12MHz C7424717; Crystal_SMD_3225-4Pin_3.2x2.5mm

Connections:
+3V3: C51.1, U11.16 (VCC); also elsewhere on the board
/CH340_DEBUG/FRONT_PANEL.D+: U11.5 (UD+); also elsewhere on the board
/CH340_DEBUG/FRONT_PANEL.D-: U11.6 (UD-); also elsewhere on the board
/CH340_DEBUG/RXD: R21.1, U11.3 (RXD)
/CH340_DEBUG/TXD: R20.1, U11.2 (TXD)
/CH340_DEBUG/UART_DEBUG.RX: R20.2; also elsewhere on the board
/CH340_DEBUG/UART_DEBUG.TX: R21.2; also elsewhere on the board
GND: C51.2, C52.2, C53.2, C54.2, U11.1 (GND), Y2.2, Y2.4; also elsewhere on the board
unnamed: C52.1, U11.4 (V3)
unnamed: C53.1, U11.7 (XI), Y2.3
unnamed: C54.1, U11.8 (XO), Y2.1

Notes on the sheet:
UART RX TX FLIP HERE

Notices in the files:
parts and their libraries:
License: Apache-2.0
